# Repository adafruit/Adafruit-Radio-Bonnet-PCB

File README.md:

## Adafruit LoRa Radio Bonnet with OLED - RFM95W @ 915MHz - RadioFruit PCB

<a href="http://www.adafruit.com/products/4074"><br/>
Click here to purchase one from the Adafruit shop</a>

PCB files for the Adafruit LoRa Radio Bonnet with OLED - RFM95W @ 915MHz - RadioFruit. Format is EagleCAD schematic and board layout
* https://www.adafruit.com/product/4074

### Description

The latest Raspberry Pi computers come with WiFi and Bluetooth, and now you can add even more radio options with the Adafruit Radio Bonnets! Upgrade your Raspberry Pi with a LoRa / LoRaWAN radio, so it can communicate over very long distances. These bonnets plug right into your Pi and give you long range wireless capabilities to remote nodes that may be battery powered. Or, you can create Internet gateways with ease.

You not only get a radio module, but also a 128x32 OLED display for status messages and three buttons you can use for creating a custom user interface or sending test messages. All of the above is supported with our Python libraries so you can send or receive LoRa data with other matching modules, send data to a LoRaWAN gateway, or even set up your own single channel LoRaWAN-to-Internet gateways.

Compared to the 2.4 GHz WiFi/Bluetooth radios on the Pi already, these modules run at 433 or 900 MHz (sub-GHz). You can't send data as fast but you can send data a lot farther. These packet radios are simpler than WiFi or BLE, you don't have to associate, pair, scan, or worry about connections. All you do is send data whenever you like, and any other modules tuned to that same frequency (and, with the same encryption key) will receive. The receiver can then send a reply back. The modules do packetization, error correction and can also auto-retransmit so it's not like you have worry about everything but less power is wasted on maintaining a link or pairing.

These modules are great for use with other microcontrollers with matching radios (like say our [RadioFruit Feathers](https://www.adafruit.com/?q=radiofruit%20feather)), say if you want a sensor node network or transmit data over a campus or town. The trade off is you need two or more radios, with matching frequencies.

These radio modules come in four variants (two modulation types and two frequencies) The RFM69's are easiest to work with, and are well known and understood. The LoRa radios are exciting and more powerful but also more expensive.

**This is the 900 MHz LoRa radio version, which can be used for either 868MHz or 915MHz transmission/reception** - the exact radio frequency is determined when you load the software since it can be tuned around dynamically. These are +20dBm LoRa packet radios that have a special radio modulation that is not compatible with the RFM69s but can go much much farther. They can easily go 2 Km line of sight using simple wire antennas, or up to 20Km with directional antennas and settings tweakings

 * Packet radio with ready-to-go CircuitPython libraries
 * Uses the license-free ISM band: "European ISM" @ 868MHz or "American ISM" @ 915MHz
 * Use a simple wire antenna or spot for uFL or SMA radio connector
 * SX1276 LoRa® based module with SPI interface
 * +5 to +20 dBm up to 100 mW Power Output Capability (power output selectable in software)
 * ~100mA peak during +20dBm transmit, ~30mA during active radio listening.
 * Range of approx. 2Km, depending on obstructions, frequency, antenna and power output
All radios are sold individually and can only talk to radios of the same part number. E.g. RFM69 900 MHz can only talk to RFM69 900 MHz, LoRa 433 MHz can only talk to LoRa 433, etc.

Each bonnet comes fully assembled and ready to go. You can attach an antenna via the uFL connector, or cut and solder on a small piece of wire (any solid or stranded core is fine) in order to create your antenna.

### License

Adafruit invests time and resources providing this open source design, please support Adafruit and open-source hardware by purchasing products from [Adafruit](https://www.adafruit.com)!

Designed by Limor Fried/Ladyada for Adafruit Industries.

Creative Commons Attribution/Share-Alike, all text above must be included in any redistribution. See license.txt for additional details.

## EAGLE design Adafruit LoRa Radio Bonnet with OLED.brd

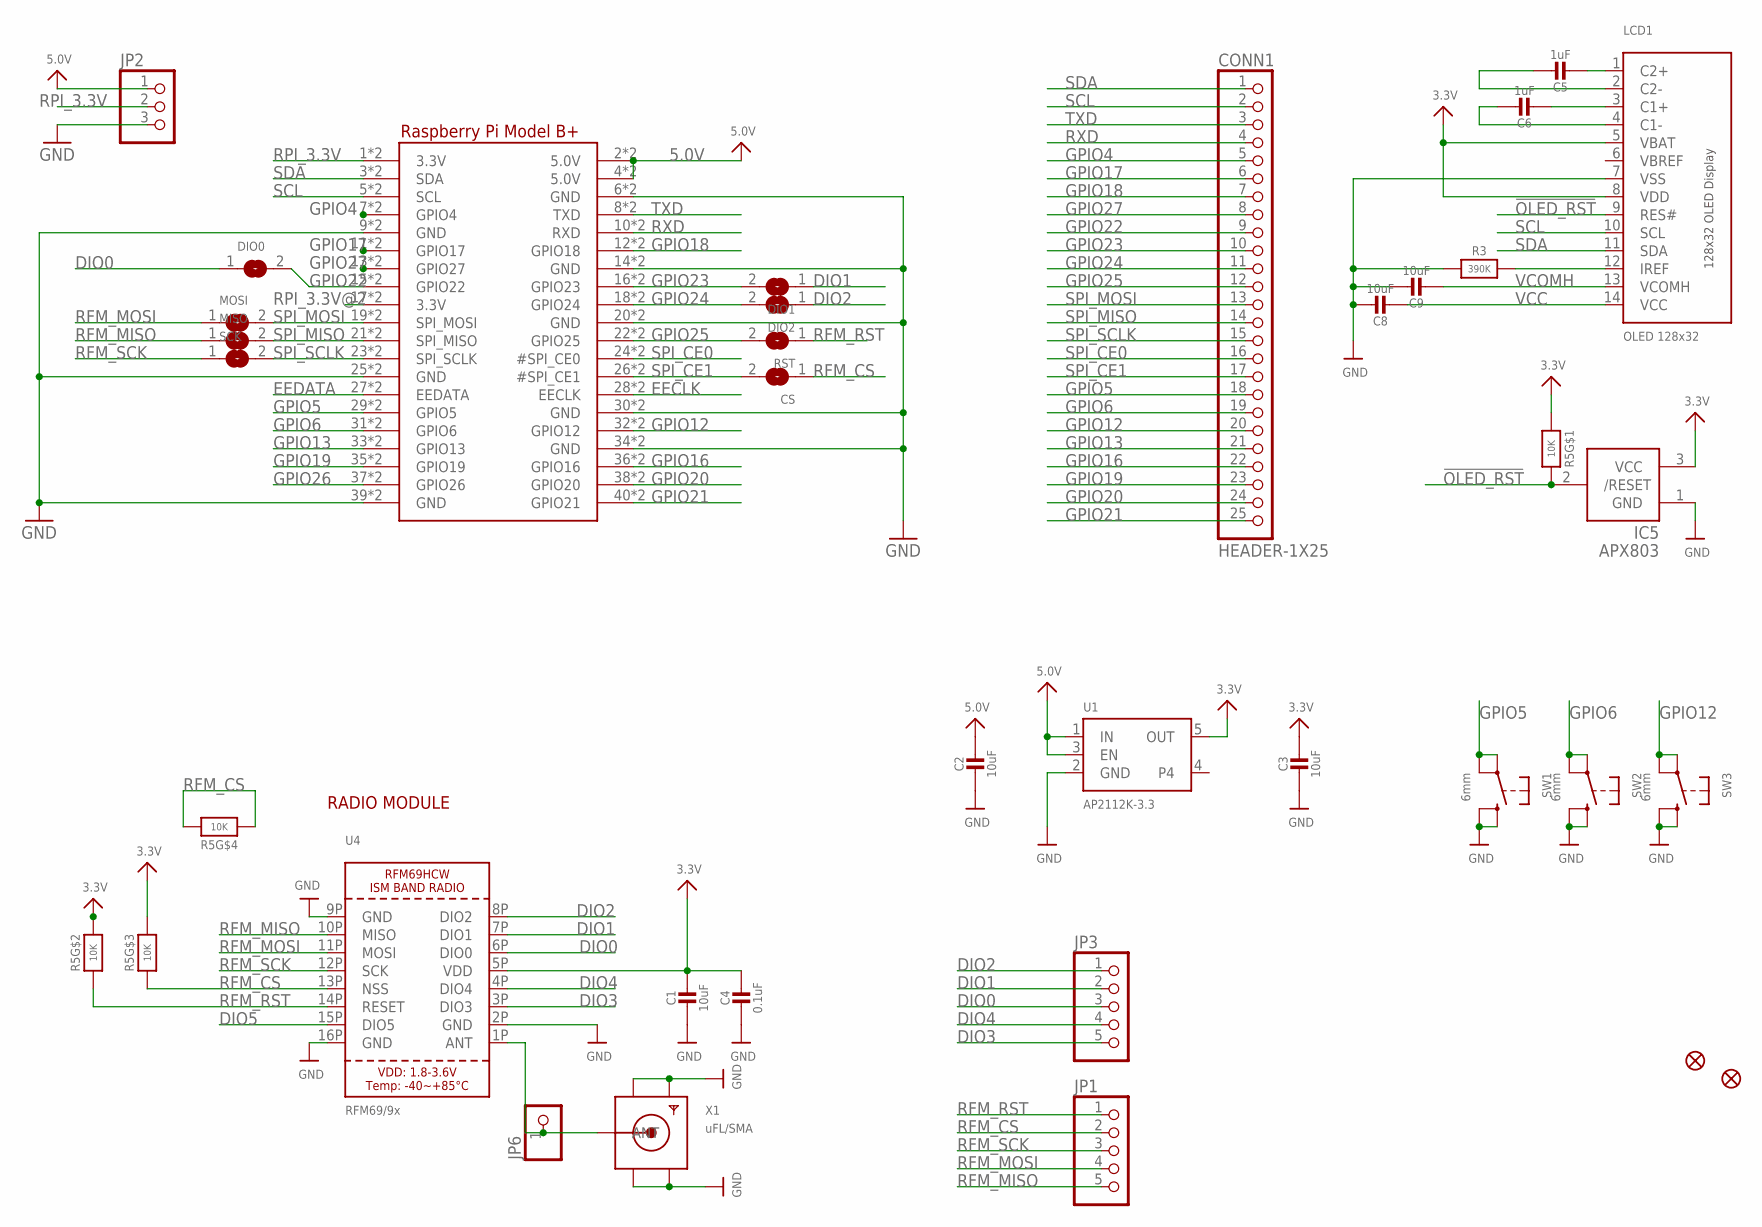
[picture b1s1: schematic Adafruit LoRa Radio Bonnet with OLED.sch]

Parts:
C1, C2, C3, C8, C9: 10uF; 0805-NO
C4: 0.1uF; 0603-NO
C5, C6: 1uF; 0603-NO
CONN1: HEADER-1X25; 1X25_ROUND_70MIL
CS: SOLDERJUMPERCLOSED; SOLDERJUMPER_CLOSEDWIRE
DIO0, DIO1, DIO2: SOLDERJUMPERCLOSED; SOLDERJUMPER_CLOSEDWIRE
FID1, FID2: FIDUCIAL_1MM
IC5: APX803; SOT23
JP1, JP3: HEADER-1X570MIL; 1X05_ROUND_70
JP2: HEADER-1X3ROUND; 1X03_ROUND
JP6: HEADER-1X1ROUND; 1X01_ROUND
LCD1: OLED 128x32; UG-2832HSWEG02_WRAPUNDER
MISO: SOLDERJUMPERCLOSED; SOLDERJUMPER_CLOSEDWIRE
MOSI: SOLDERJUMPERCLOSED; SOLDERJUMPER_CLOSEDWIRE
R3: 390K; 0603-NO
R5: 10K; RESPACK_4X0603
RPI1: RASPBERRYPI_BPLUS_BONNET_THMSMT; PI_BONNET_THMSMT
RST: SOLDERJUMPERCLOSED; SOLDERJUMPER_CLOSEDWIRE
SCK: SOLDERJUMPERCLOSED; SOLDERJUMPER_CLOSEDWIRE
SW1, SW2, SW3: 6mm; EVQ-Q2_SMALLER
U1: AP2112K-3.3; SOT23-5
U4: RFM69/9x; RFMHCW_SMT
X1: uFL/SMA; SMA_EDGELAUNCH_UFL

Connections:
3.3V: C1.1, C3.1, C4.1, IC5.3 (VCC), LCD1.5 (VBAT), LCD1.8 (VDD), R5.1, R5.6 (2), R5.7 (2), U1.5 (OUT), U4.5P (VDD)
5.0V: C2.1, JP2.1, RPI1.2 (5.0V), RPI1.4 (5.0V), RPI1.S2 (5.0V), RPI1.S4 (5.0V), U1.1 (IN), U1.3 (EN)
!OLED_RST: IC5.2 (/RESET), LCD1.9 (RES#), R5.8 (2)
ANT: JP6.1, U4.1P (ANT), X1.P (ANT)
DIO0: DIO0.1, JP3.3, U4.6P (DIO0)
DIO1: DIO1.1, JP3.2, U4.7P (DIO1)
DIO2: DIO2.1, JP3.1, U4.8P (DIO2)
DIO3: JP3.5, U4.3P (DIO3)
DIO4: JP3.4, U4.4P (DIO4)
DIO5: U4.15P (DIO5)
EECLK: RPI1.28 (EECLK), RPI1.S28 (EECLK)
EEDATA: RPI1.27 (EEDATA), RPI1.S27 (EEDATA)
GND: C1.2, C2.2, C3.2, C4.2, C8.1, C9.1, IC5.1 (GND), JP2.3, LCD1.7 (VSS), R3.1, RPI1.6 (GND), RPI1.9 (GND), RPI1.14 (GND), RPI1.20 (GND), RPI1.25 (GND), RPI1.30 (GND), RPI1.34 (GND), RPI1.39 (GND), RPI1.S6 (GND), RPI1.S9 (GND), RPI1.S14 (GND), RPI1.S20 (GND), RPI1.S25 (GND), RPI1.S30 (GND), RPI1.S34 (GND), RPI1.S39 (GND), SW1.B (S), SW1.B' (S1), SW2.B (S), SW2.B' (S1), SW3.B (S), SW3.B' (S1), U1.2 (GND), U4.2P (GND), U4.9P (GND), U4.16P (GND), X1.GND@1 (GND1), X1.GND@2 (GND2), X1.GND@3 (GND3), X1.GND@4 (GND4)
GPIO4: CONN1.5, RPI1.7 (GPIO4), RPI1.S7 (GPIO4)
GPIO5: CONN1.18, RPI1.29 (GPIO5), RPI1.S29 (GPIO5), SW1.A, SW1.A' (P1)
GPIO6: CONN1.19, RPI1.31 (GPIO6), RPI1.S31 (GPIO6), SW2.A, SW2.A' (P1)
GPIO12: CONN1.20, RPI1.32 (GPIO12), RPI1.S32 (GPIO12), SW3.A, SW3.A' (P1)
GPIO13: CONN1.21, RPI1.33 (GPIO13), RPI1.S33 (GPIO13)
GPIO16: CONN1.22, RPI1.36 (GPIO16), RPI1.S36 (GPIO16)
GPIO17: CONN1.6, RPI1.11 (GPIO17), RPI1.S11 (GPIO17)
GPIO18: CONN1.7, RPI1.12 (GPIO18), RPI1.S12 (GPIO18)
GPIO19: CONN1.23, RPI1.35 (GPIO19), RPI1.S35 (GPIO19)
GPIO20: CONN1.24, RPI1.38 (GPIO20), RPI1.S38 (GPIO20)
GPIO21: CONN1.25, RPI1.40 (GPIO21), RPI1.S40 (GPIO21)
GPIO22: CONN1.9, DIO0.2, RPI1.15 (GPIO22), RPI1.S15 (GPIO22)
GPIO23: CONN1.10, DIO1.2, RPI1.16 (GPIO23), RPI1.S16 (GPIO23)
GPIO24: CONN1.11, DIO2.2, RPI1.18 (GPIO24), RPI1.S18 (GPIO24)
GPIO25: CONN1.12, RPI1.22 (GPIO25), RPI1.S22 (GPIO25), RST.2
GPIO26: RPI1.37 (GPIO26), RPI1.S37 (GPIO26)
GPIO27: CONN1.8, RPI1.13 (GPIO27), RPI1.S13 (GPIO27)
unnamed: C5.2, LCD1.1 (C2+)
unnamed: C5.1, LCD1.2 (C2-)
unnamed: C6.2, LCD1.3 (C1+)
unnamed: C6.1, LCD1.4 (C1-)
unnamed: LCD1.12 (IREF), R3.2
RFM_CS: CS.1, JP1.2, R5.3 (1), R5.4 (1), R5.5 (2), U4.13P (NSS)
RFM_MISO: JP1.5, MISO.1, U4.10P (MISO)
RFM_MOSI: JP1.4, MOSI.1, U4.11P (MOSI)
RFM_RST: JP1.1, R5.2 (1), RST.1, U4.14P (RESET)
RFM_SCK: JP1.3, SCK.1, U4.12P (SCK)
RPI_3.3V: JP2.2, RPI1.1 (3.3V), RPI1.S1 (3.3V)
RPI_3.3V@2: RPI1.17 (3.3V), RPI1.S17 (3.3V)
RXD: CONN1.4, RPI1.10 (RXD), RPI1.S10 (RXD)
SCL: CONN1.2, LCD1.10 (SCL), RPI1.5 (SCL), RPI1.S5 (SCL)
SDA: CONN1.1, LCD1.11 (SDA), RPI1.3 (SDA), RPI1.S3 (SDA)
SPI_CE0: CONN1.16, RPI1.24 (#SPI_CE0), RPI1.S24 (#SPI_CE0)
SPI_CE1: CONN1.17, CS.2, RPI1.26 (#SPI_CE1), RPI1.S26 (#SPI_CE1)
SPI_MISO: CONN1.14, MISO.2, RPI1.21 (SPI_MISO), RPI1.S21 (SPI_MISO)
SPI_MOSI: CONN1.13, MOSI.2, RPI1.19 (SPI_MOSI), RPI1.S19 (SPI_MOSI)
SPI_SCLK: CONN1.15, RPI1.23 (SPI_SCLK), RPI1.S23 (SPI_SCLK), SCK.2
TXD: CONN1.3, RPI1.8 (TXD), RPI1.S8 (TXD)
VBREF: LCD1.6 (VBREF)
VCC: C8.2, LCD1.14 (VCC)
VCOMH: C9.2, LCD1.13 (VCOMH)

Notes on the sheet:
RADIO MODULE

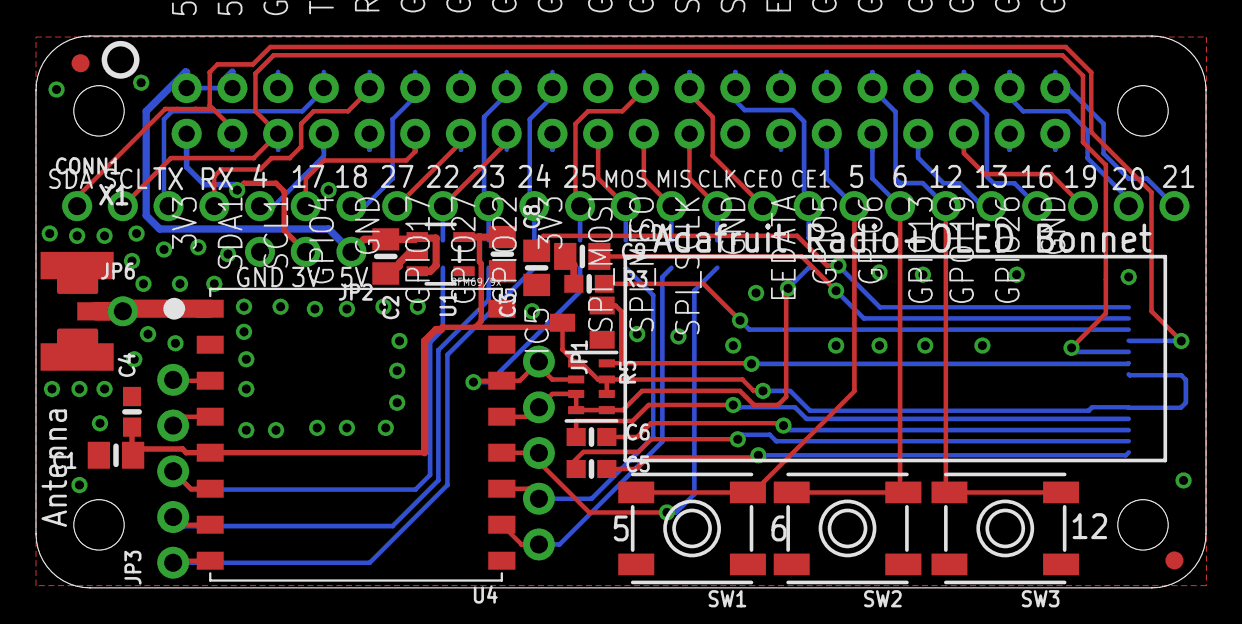
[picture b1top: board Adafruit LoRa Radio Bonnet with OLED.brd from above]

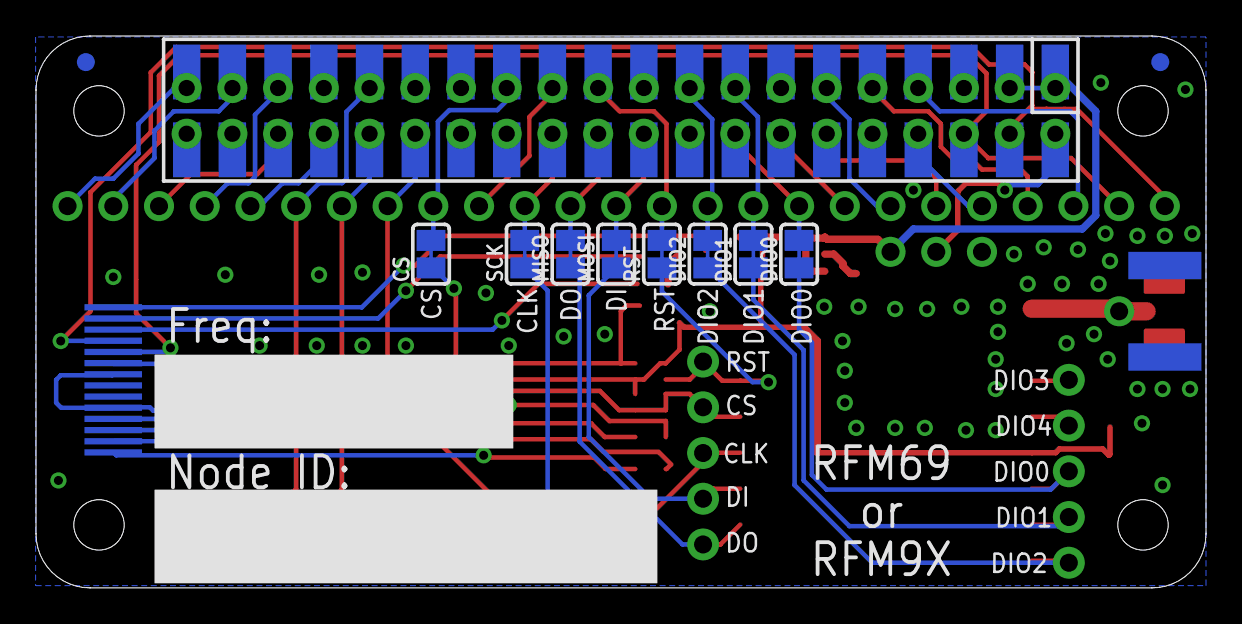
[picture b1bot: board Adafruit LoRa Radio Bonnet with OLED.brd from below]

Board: 2 copper layers, 65.0 x 30.7 mm, 35 parts (8 on the bottom side), 52 nets.

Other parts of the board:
U$22: PCBFEAT-REV-040

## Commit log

2019-01-19 Add sch and brd files.
2019-01-19 Update README.
2019-07-17 updated to use cookiecutter for pcb repos

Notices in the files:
parts and their libraries:
microbuilder: This work is placed in the public domain, and may be freely used for commercial and non-commercial work with the following conditions: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
